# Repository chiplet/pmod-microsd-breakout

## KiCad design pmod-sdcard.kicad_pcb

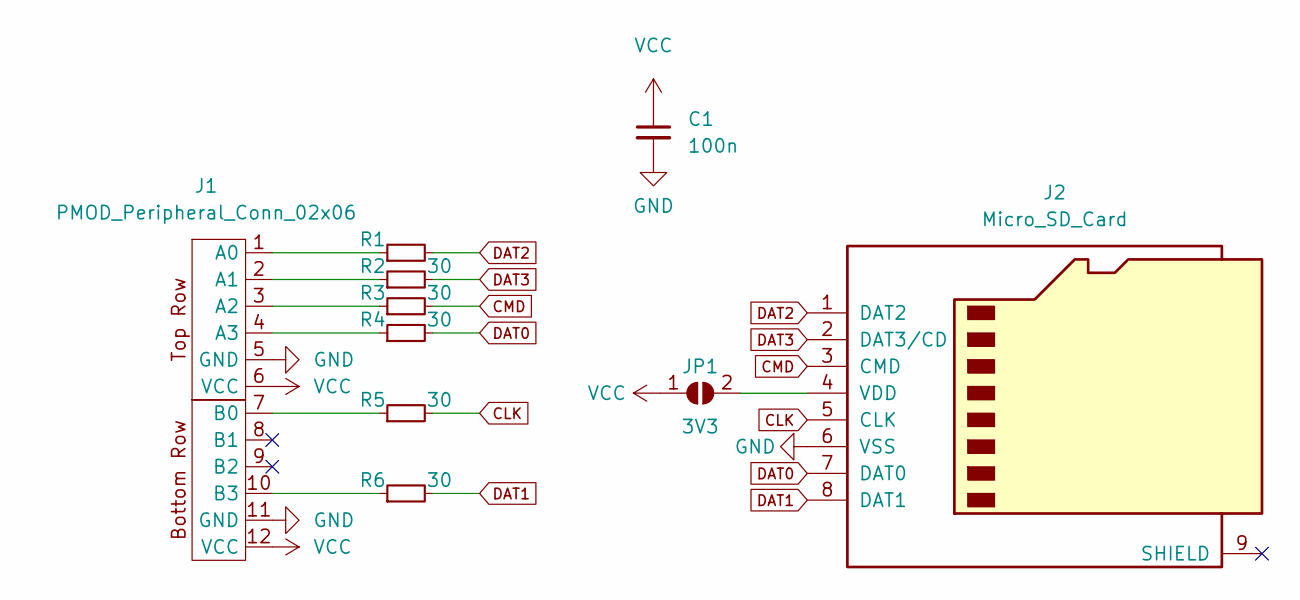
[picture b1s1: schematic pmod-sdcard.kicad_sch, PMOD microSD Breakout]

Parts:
C1: 100n; C_0603_1608Metric_Pad1.08x0.95mm_HandSolder
J1: PMOD_Peripheral_Conn_02x06; PMOD_PinHeader_2x06_P2.54mm_Horizontal
J2: Micro_SD_Card; microSD
JP1: 3V3; SolderJumper-2_P1.3mm_Open_RoundedPad1.0x1.5mm
R1: (no value)
R2, R3, R4, R5, R6: 30

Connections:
CLK: J2.5 (CLK), R5.2
CMD: J2.3 (CMD), R3.2
DAT0: J2.7 (DAT0), R4.2
DAT1: J2.8 (DAT1), R6.2
DAT2: J2.1 (DAT2), R1.2
DAT3: J2.2 (DAT3/CD), R2.2
GND: C1.2, J1.5 (GND), J1.11 (GND), J2.6 (VSS)
unnamed: J1.1 (A0), R1.1
unnamed: J1.2 (A1), R2.1
unnamed: J1.3 (A2), R3.1
unnamed: J1.4 (A3), R4.1
unnamed: J1.7 (B0), R5.1
unnamed: J1.10 (B3), R6.1
unnamed: J2.4 (VDD), JP1.2 (B)
VCC: C1.1, J1.6 (VCC), J1.12 (VCC), JP1.1 (A)

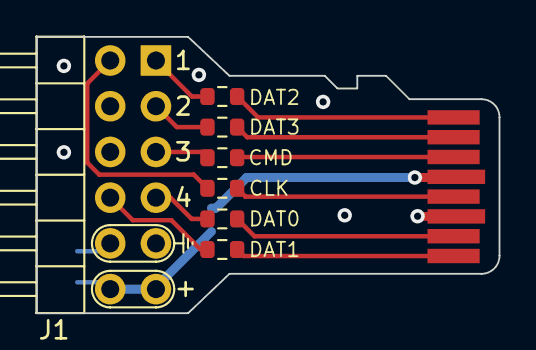
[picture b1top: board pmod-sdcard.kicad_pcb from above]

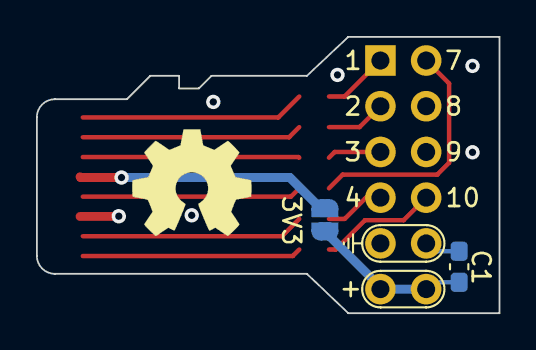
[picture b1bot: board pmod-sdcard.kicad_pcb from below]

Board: 4 copper layers, 25.7 x 15.4 mm, 10 parts (2 on the bottom side), 15 nets.

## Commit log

2022-05-18 Tweak component placement
2022-05-18 Run DRC and fix warnings
2022-05-18 Check in gerbers
2022-06-22 Add series resistors for signal lines
